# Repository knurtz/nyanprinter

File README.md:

# NyanPrinter
This printer runs on STM32F103 and it prints AND plays the nyan cat!

## Idea

Thermal printers make a lot of noise while printing -- everyone, who has bought something from a shop with one of those old cash registers knows that! At the heart of such a printer lies of course a stepper motor. Making music with stepper motors is an old thing in the Arduino community. But as far as I know, nobody has ever tried to make music AND print something at the same time -- until now!

Getting picture and sound to line up is not particulary easy, because there are certain limitations to the printing speed of a thermal printer -- and thus also for the maximum pitch we can get out of the machine. 

The datasheet recommends an approximate exposure of 1 ms per line, which responds to a 1 kHz pitch. This is, unless more than 64 pixels out of the total 384 pixels per line are printed simultanously. Here we need to do devided printing, which means multiple exposure bursts for one single line. This is where things get tricky. I need to let the printer run at a fixed speed and cannot stop at a line just because I want to print more than 64 pixels. Otherwise I would get a sudden break in my music.

This is the solution I came up with: If the printer encounters a line with more than 64 pixels, it prints the first 64 (or less) pixels, then advances the motor one step, going back one step immediately in order to print the next 64 pixels and so on. I have not yet tested, if the sudden change in direction is audible. If so, I might have to change it up a little bit and print multiple lines first, then go back over them a second time.

## Hardware

- STM32F103 Bluepill Development Board: [stm32duino.com](https://web.archive.org/web/20190524151648/https://wiki.stm32duino.com/index.php?title=Blue_Pill)
- Thermal printer MATSUSHITA EPL1801S2E from [pollin.de](https://www.pollin.de/p/thermo-druckelement-matsushita-epl1801s2e-721066)
- an awesome huge blue push button from [Amazon](https://www.amazon.de/gp/product/B07BSFMZJ2) (it lights up, too!)
- A4988 stepper motor driver board like this one from [pololu.com](https://www.pololu.com/product/1182)
- RECOM R-78E5.0-0.5 DC/DC converter from [conrad.de](https://www.conrad.de/de/recom-r-78e50-05-dcdc-wandler-print-24-vdc-5-vdc-500-ma-anzahl-ausgaenge-1-x-157954.html?)
- MAX6966 led driver from [farnell.com](https://de.farnell.com/maxim-integrated-products/max6966aee/led-treiber-mit-i-o-erweiterung/dp/2516036) for fancy led stuff
- custom milled PCB with some additional components like resistors and capacitors (Eagle files following shortly)
- custom enclosure printed with the amazing Vertigo Starlight filament from [filamentworld.de](https://www.filamentworld.de/shop/pla-filament-3d-drucker/pla-filament-1-75-mm-vertigo-starlight-075-kg/) (STL files following shortly as well)

## Software

I wanted to learn more about hardware peripherals of the STM32 family in this project. This is why I use a total of 3 timers, 2 DMA channels, one SPI and one UART peripheral. Things could have probably be done less complicated, but I would not have learned anything the easy way.

TIM2 is responsible for the motor step signal. It runs at a frequency that is determined by the current pitch of the music. The motor driver makes a step at every rising edge of the signal. Also, the printer needs to advance two steps for every line. Because of that, at every update interrupt of TIM2 (which corresponds to every step of the motor) I alternate between sending new data to the printer (triggering TIM1) and starting the exposure (triggering TIM3).

Data transfer is timed by TIM1, which triggers 64 DMA requests (64 transfers * 6 "pixels" per transfer = 384 pixels per line). The DMA sends the data to 6 parallel data lines that go into 6 shift registers inside the printer. Data alignment looks weird, this is why I wrote a small python script to convert images to a special byte array.

Finally TIM3 creates a pulse that corresponds to the needed exposure time of about 750 - 1000 us (depending on the supply voltage).

UART is needed for debugging and SPI for the led driver.

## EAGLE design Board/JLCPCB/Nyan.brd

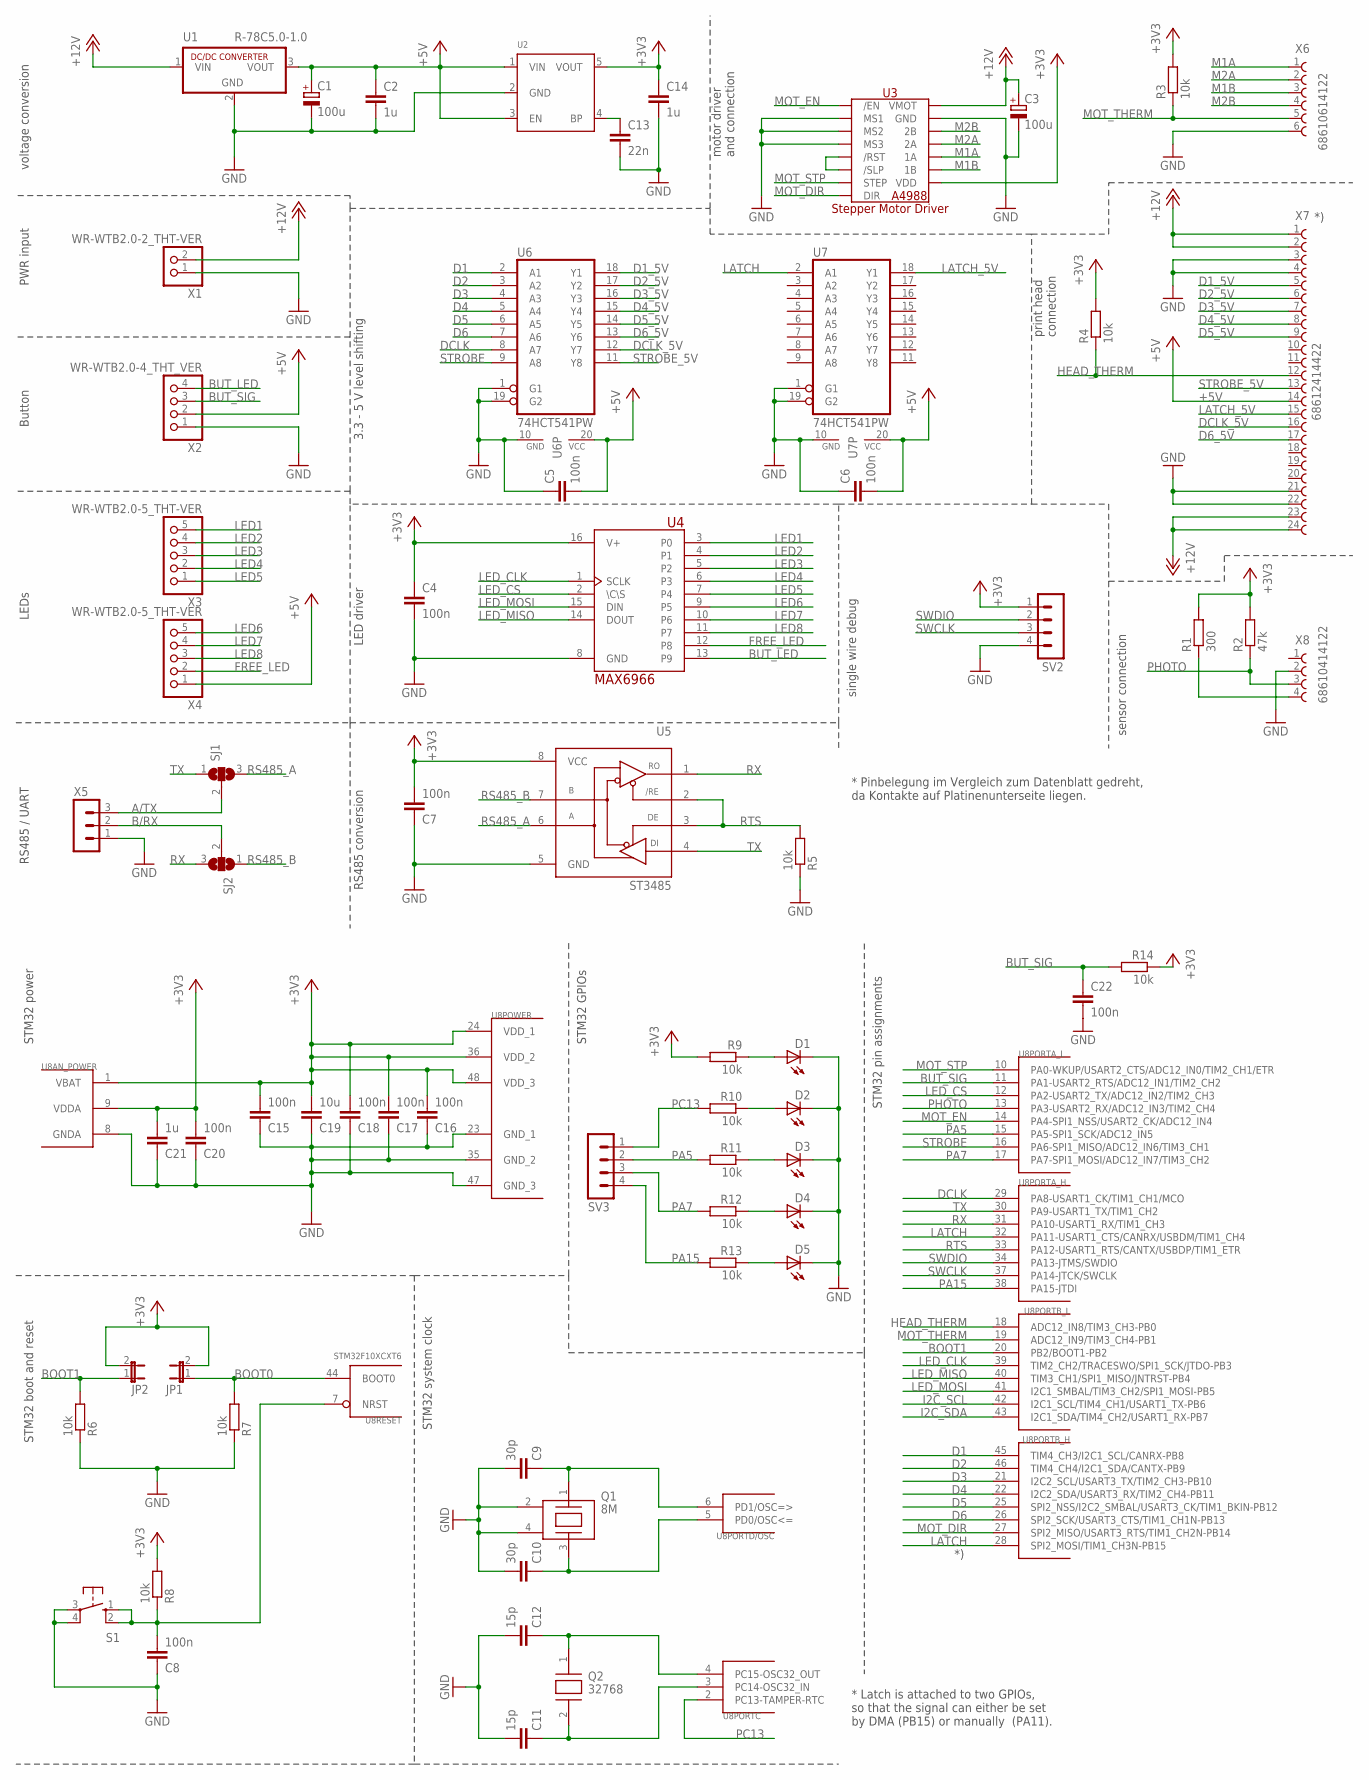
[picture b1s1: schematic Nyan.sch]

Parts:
C1, C3: 100u; E2,5-6
C2, C14, C21: 1u; C0603
C4, C5, C6, C7, C8, C15, C16, C17, C18, C20, C22: 100n; C0603
C9, C10: 30p; C0603
C11, C12: 15p; C0603
C13: 22n; C0603
C19: 10u; C0603
D1, D2, D3, D4, D5: LEDCHIP-LED0603; CHIP-LED0603
JP1, JP2: JP1E; JP1
Q1: 8M; SMD_5X3.2
Q2: 32768; SMD_3.2X1.5
R1: 300; R0603
R2: 47k; R0603
R3, R4, R5, R6, R7, R8, R9, R10, R11, R12, R13, R14: 10k; R0603
S1: 6X6_MOMENTARY_SWITCH
SJ1, SJ2: SJ2W; SJ_2
SV2, SV3: MA04-1ROUND_PAD; MA04-1_ROUND
U1: R-78C5.0-1.0; SIP3
U2: RT9193; SOT23-5
U3: A4988_STEP
U4: MAX6966; QSOP-16
U5: ST3485; SO-08
U6, U7: 74HCT541PW; TSSOP20
U8: STM32F10XCXT6; TQFP48
X1: WR-WTB2.0-2_THT-VER; WR-WTB2.0-2-THT-VER
X2: WR-WTB2.0-4_THT_VER; WR-WTB2.0-4-THT-VER
X3, X4: WR-WTB2.0-5_THT-VER; WR-WTB2.0-5-THT-VER
X5: MA03-1ROUND_PAD; MA03-1_ROUND
X6: 68610614122
X7: 68612414422
X8: 68610414122

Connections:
+3V3: C4.1, C7.2, C14.1, C15.2, C16.2, C17.2, C18.2, C19.2, C20.2, C21.2, JP1.2, JP2.2, R1.2, R2.2, R3.2, R4.2, R8.2, R9.2, R14.1, SV2.1, U2.5 (VOUT), U3.VDD, U4.16 (V+), U5.8 (VCC), U8.1 (VBAT), U8.9 (VDDA), U8.24 (VDD_1), U8.36 (VDD_2), U8.48 (VDD_3)
+5V: C1.+, C2.1, C5.2, C6.2, U1.3 (VOUT), U2.1 (VIN), U2.3 (EN), U6.20 (VCC), U7.20 (VCC), X2.2, X4.1, X7.14
+12V: C3.+, U1.1 (VIN), U3.VMOT, X1.2, X7.1, X7.2, X7.23, X7.24
A/TX: SJ1.2, X5.3
B/RX: SJ2.2, X5.2
BOOT0: JP1.1, R7.2, U8.44 (BOOT0)
BOOT1: JP2.1, R6.2, U8.20 (PB2/BOOT1-PB2)
BUT_LED: U4.13 (P9), X2.4
BUT_SIG: C22.1, R14.2, U8.11 (PA1-USART2_RTS/ADC12_IN1/TIM2_CH2), X2.3
D1: U6.2 (A1), U8.45 (TIM4_CH3/I2C1_SCL/CANRX-PB8)
D1_5V: U6.18 (Y1), X7.5
D2: U6.3 (A2), U8.46 (TIM4_CH4/I2C1_SDA/CANTX-PB9)
D2_5V: U6.17 (Y2), X7.6
D3: U6.4 (A3), U8.21 (I2C2_SCL/USART3_TX/TIM2_CH3-PB10)
D3_5V: U6.16 (Y3), X7.7
D4: U6.5 (A4), U8.22 (I2C2_SDA/USART3_RX/TIM2_CH4-PB11)
D4_5V: U6.15 (Y4), X7.8
D5: U6.6 (A5), U8.25 (SPI2_NSS/I2C2_SMBAL/USART3_CK/TIM1_BKIN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)
D5_5V: U6.14 (Y5), X7.9
D6: U6.7 (A6), U8.26 (SPI2_SCK/USART3_CTS/TIM1_CH1N-PB13)
D6_5V: U6.13 (Y6), X7.17
DCLK: U6.8 (A7), U8.29 (PA8-USART1_CK/TIM1_CH1/MCO)
DCLK_5V: U6.12 (Y7), X7.16
FREE_LED: U4.12 (P8), X4.2
GND: C1.-, C2.2, C3.-, C4.2, C5.1, C6.1, C7.1, C8.1, C9.2, C10.2, C11.2, C12.2, C13.2, C14.2, C15.1, C16.1, C17.1, C18.1, C19.1, C20.1, C21.1, C22.2, D1.C, D2.C, D3.C, D4.C, D5.C, Q1.2, Q1.4, R5.1, R6.1, R7.1, S1.3, S1.4, SV2.4, U1.2 (GND), U2.2 (GND), U3.GND, U3.GND2 (GND), U3.MS1, U3.MS2, U3.MS3, U4.8 (GND), U5.5 (GND), U6.1 (G1), U6.10 (GND), U6.19 (G2), U7.1 (G1), U7.10 (GND), U7.19 (G2), U8.8 (GNDA), U8.23 (GND_1), U8.35 (GND_2), U8.47 (GND_3), X1.1, X2.1, X5.1, X6.6, X7.3, X7.4, X7.21, X7.22, X8.2
HEAD_THERM: R4.1, U8.18 (ADC12_IN8/TIM3_CH3-PB0), X7.12
I2C_SCL: U8.42 (I2C1_SCL/TIM4_CH1/USART1_TX-PB6)
I2C_SDA: U8.43 (I2C1_SDA/TIM4_CH2/USART1_RX-PB7)
LATCH: U7.2 (A1), U8.28 (SPI2_MOSI/TIM1_CH3N-PB15), U8.32 (PA11-USART1_CTS/CANRX/USBDM/TIM1_CH4)
LATCH_5V: U7.18 (Y1), X7.15
LED1: U4.3 (P0), X3.5
LED2: U4.4 (P1), X3.4
LED3: U4.5 (P2), X3.3
LED4: U4.6 (P3), X3.2
LED5: U4.7 (P4), X3.1
LED6: U4.9 (P5), X4.5
LED7: U4.10 (P6), X4.4
LED8: U4.11 (P7), X4.3
LED_CLK: U4.1 (SCLK), U8.39 (TIM2_CH2/TRACESWO/SPI1_SCK/JTDO-PB3)
LED_CS: U4.2 (\C\S), U8.12 (PA2-USART2_TX/ADC12_IN2/TIM2_CH3)
LED_MISO: U4.14 (DOUT), U8.40 (TIM3_CH1/SPI1_MISO/JNTRST-PB4)
LED_MOSI: U4.15 (DIN), U8.41 (I2C1_SMBAL/TIM3_CH2/SPI1_MOSI-PB5)
M1A: U3.1A, X6.1
M1B: U3.1B, X6.3
M2A: U3.2A, X6.2
M2B: U3.2B, X6.4
MOT_DIR: U3.DIR, U8.27 (SPI2_MISO/USART3_RTS/TIM1_CH2N-PB14)
MOT_EN: U3./EN, U8.14 (PA4-SPI1_NSS/USART2_CK/ADC12_IN4)
MOT_STP: U3.STEP, U8.10 (PA0-WKUP/USART2_CTS/ADC12_IN0/TIM2_CH1/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)
MOT_THERM: R3.1, U8.19 (ADC12_IN9/TIM3_CH4-PB1), X6.5
unnamed: R1.1, X8.4
unnamed: U3./RST, U3./SLP
unnamed: C8.2, R8.1, S1.1, S1.2, U8.7 (NRST)
unnamed: C12.1, Q2.1, U8.4 (PC15-OSC32_OUT)
unnamed: C11.1, Q2.2, U8.3 (PC14-OSC32_IN)
unnamed: C10.1, Q1.3, U8.5 (PD0/OSC<=)
unnamed: C9.1, Q1.1, U8.6 (PD1/OSC=>)
unnamed: D4.A, R12.1
unnamed: D1.A, R9.1
unnamed: D2.A, R10.1
unnamed: D3.A, R11.1
unnamed: C13.1, U2.4 (BP)
unnamed: D5.A, R13.1
PA5: R11.2, SV3.2, U8.15 (PA5-SPI1_SCK/ADC12_IN5)
PA7: R12.2, SV3.3, U8.17 (PA7-SPI1_MOSI/ADC12_IN7/TIM3_CH2)
PA15: R13.2, SV3.4, U8.38 (PA15-JTDI)
PC13: R10.2, SV3.1, U8.2 (PC13-TAMPER-RTC)
PHOTO: R2.1, U8.13 (PA3-USART2_RX/ADC12_IN3/TIM2_CH4), X8.3
RS485_A: SJ1.3, U5.6 (A)
RS485_B: SJ2.1, U5.7 (B)
RTS: R5.2, U5.2 (!RE), U5.3 (DE), U8.33 (PA12-USART1_RTS/CANTX/USBDP/TIM1_ETR)
RX: SJ2.3, U5.1 (RO), U8.31 (PA10-USART1_RX/TIM1_CH3)
STROBE: U6.9 (A8), U8.16 (PA6-SPI1_MISO/ADC12_IN6/TIM3_CH1)
STROBE_5V: U6.11 (Y8), X7.13
SWCLK: SV2.3, U8.37 (PA14-JTCK/SWCLK)
SWDIO: SV2.2, U8.34 (PA13-JTMS/SWDIO)
TX: SJ1.1, U5.4 (DI), U8.30 (PA9-USART1_TX/TIM1_CH2)

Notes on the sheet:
Button
PWR input
LEDs
RS485 / UART
* Latch is attached to two GPIOs, so that the signal can either be set by DMA (PB15) or manually (PA11).
* Pinbelegung im Vergleich zum Datenblatt gedreht, da Kontakte auf Platinenunterseite liegen.
voltage conversion
LED driver
RS485 conversion
3.3 - 5 V level shifting
motor driver and connection
print head connection
sensor connection
single wire debug
STM32 power
STM32 boot and reset
STM32 system clock
STM32 GPIOs
STM32 pin assignments

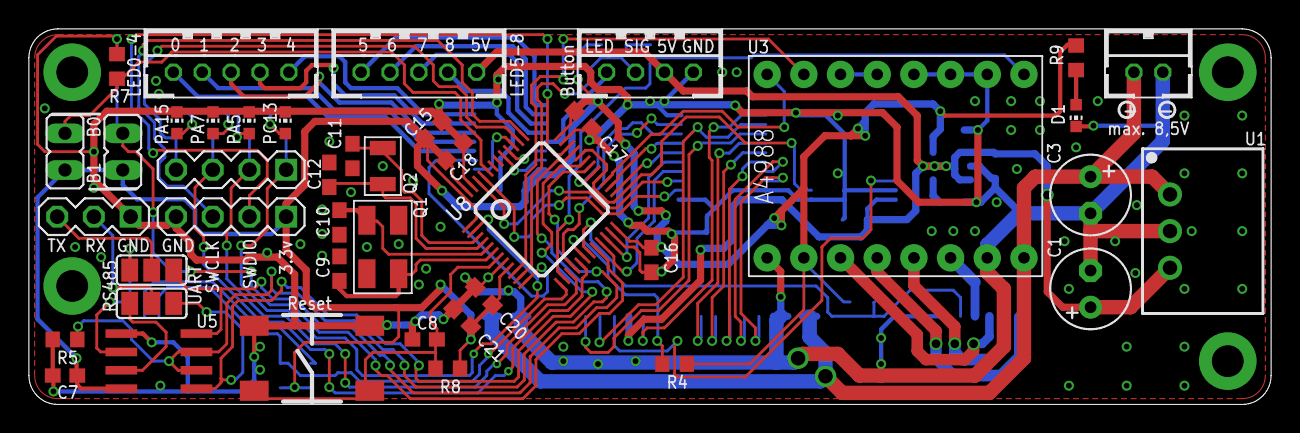
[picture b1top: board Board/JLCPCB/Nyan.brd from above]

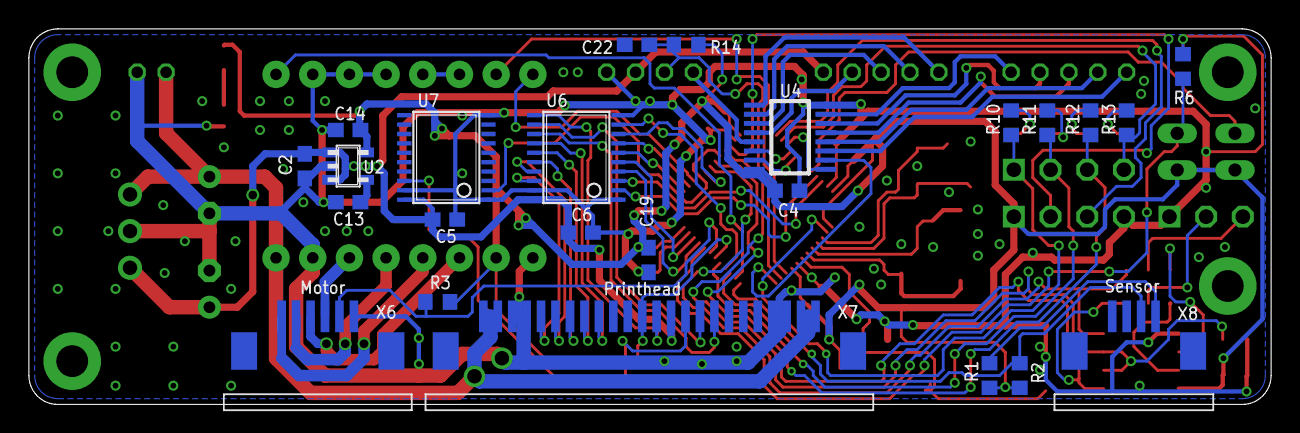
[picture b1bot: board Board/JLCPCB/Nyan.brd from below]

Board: 2 copper layers, 86.0 x 26.0 mm, 66 parts (24 on the bottom side), 75 nets.

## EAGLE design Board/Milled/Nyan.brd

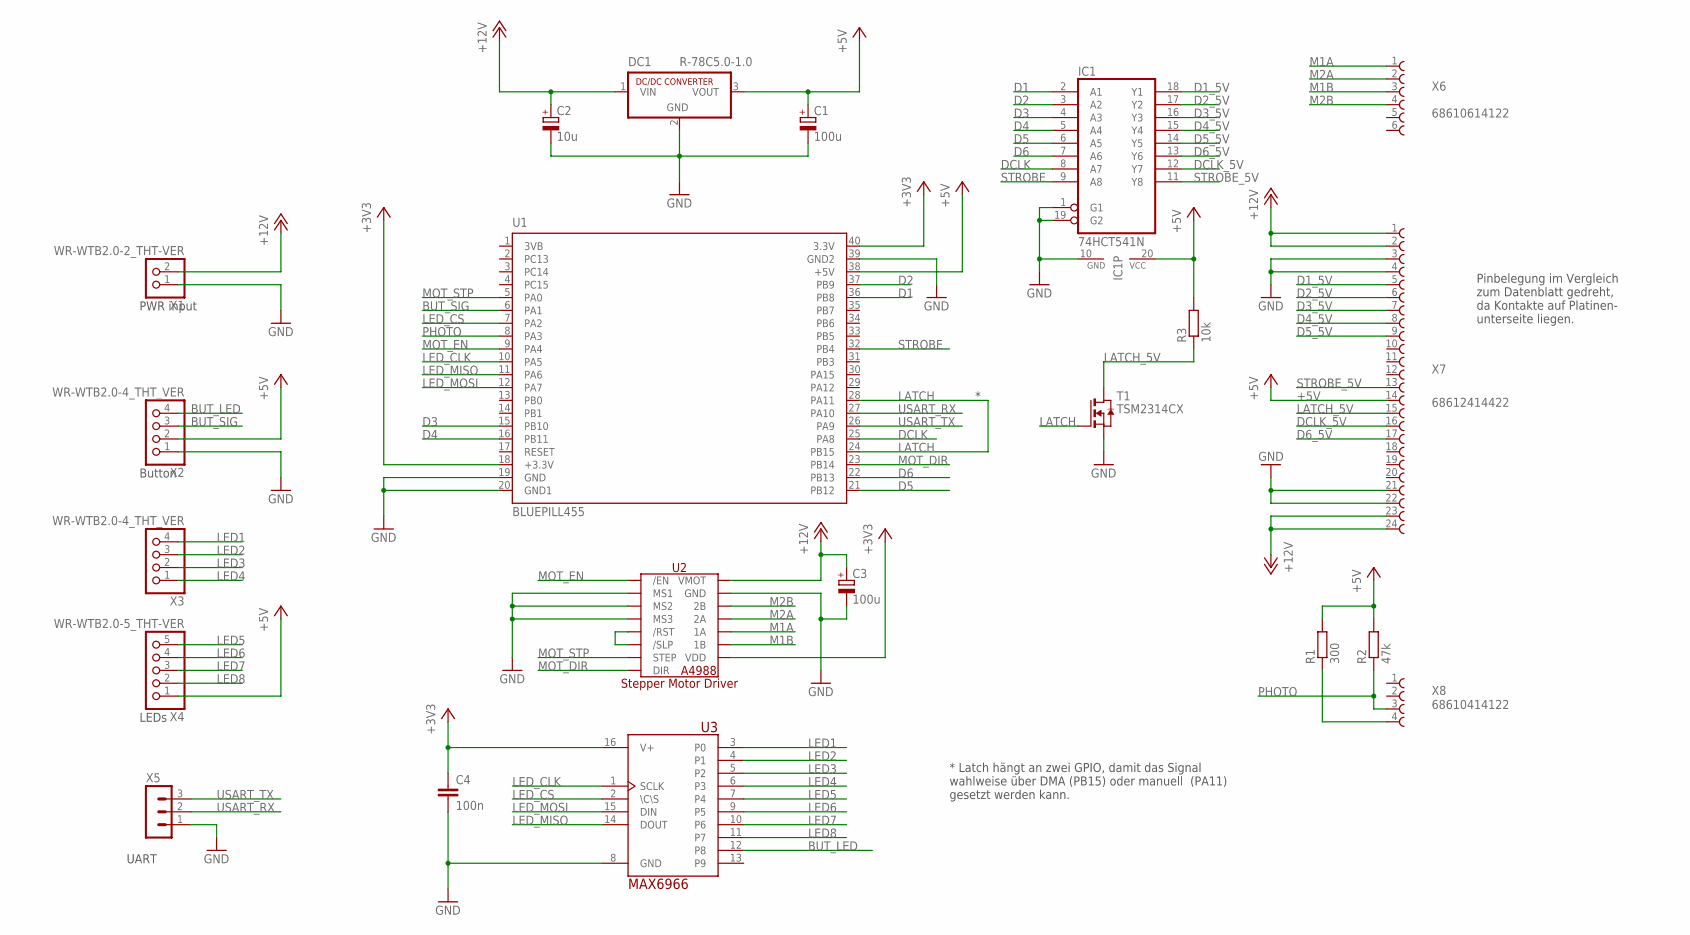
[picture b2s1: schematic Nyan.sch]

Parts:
C1, C3: 100u; E2,5-6
C2: 10u; E2,5-6
C4: 100n; C075-032X103
DC1: R-78C5.0-1.0; SIP3
IC1: 74HCT541N; DIL20
R1: 300; 0204/7
R2: 47k; 0204/7
R3: 10k; R0603
T1: TSM2314CX; SOT-23
U1: BLUEPILL455; DIL40
U2: A4988_STEP
U3: MAX6966; QSOP-16
X1: WR-WTB2.0-2_THT-VER; WR-WTB2.0-2-THT-VER
X2, X3: WR-WTB2.0-4_THT_VER; WR-WTB2.0-4-THT-VER
X4: WR-WTB2.0-5_THT-VER; WR-WTB2.0-5-THT-VER
X5: MA03-1ROUND_PAD; MA03-1_ROUND
X6: 68610614122
X7: 68612414422
X8: 68610414122

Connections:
+3V3: C4.1, U1.18 (+3.3V), U1.40 (3.3V), U2.VDD, U3.16 (V+)
+5V: C1.+, DC1.3 (VOUT), IC1.20 (VCC), R1.2, R2.2, R3.2, U1.38 (+5V), X2.2, X4.1, X7.14
+12V: C2.+, C3.+, DC1.1 (VIN), U2.VMOT, X1.2, X7.1, X7.2, X7.23, X7.24
BUT_LED: U3.12 (P8), X2.4
BUT_SIG: U1.6 (PA1), X2.3
D1: IC1.2 (A1), U1.36 (PB8)
D1_5V: IC1.18 (Y1), X7.5
D2: IC1.3 (A2), U1.37 (PB9)
D2_5V: IC1.17 (Y2), X7.6
D3: IC1.4 (A3), U1.15 (PB10)
D3_5V: IC1.16 (Y3), X7.7
D4: IC1.5 (A4), U1.16 (PB11)
D4_5V: IC1.15 (Y4), X7.8
D5: IC1.6 (A5), U1.21 (PB12)
D5_5V: IC1.14 (Y5), X7.9
D6: IC1.7 (A6), U1.22 (PB13)
D6_5V: IC1.13 (Y6), X7.17
DCLK: IC1.8 (A7), U1.25 (PA8)
DCLK_5V: IC1.12 (Y7), X7.16
GND: C1.-, C2.-, C3.-, C4.2, DC1.2 (GND), IC1.1 (G1), IC1.10 (GND), IC1.19 (G2), T1.2 (S), U1.19 (GND), U1.20 (GND1), U1.39 (GND2), U2.GND, U2.GND2 (GND), U2.MS1, U2.MS2, U2.MS3, U3.8 (GND), X1.1, X2.1, X5.1, X7.3, X7.4, X7.21, X7.22
LATCH: T1.1 (G), U1.24 (PB15), U1.28 (PA11)
LATCH_5V: R3.1, T1.3 (D), X7.15
LED1: U3.3 (P0), X3.4
LED2: U3.4 (P1), X3.3
LED3: U3.5 (P2), X3.2
LED4: U3.6 (P3), X3.1
LED5: U3.7 (P4), X4.5
LED6: U3.9 (P5), X4.4
LED7: U3.10 (P6), X4.3
LED8: U3.11 (P7), X4.2
LED_CLK: U1.10 (PA5), U3.1 (SCLK)
LED_CS: U1.7 (PA2), U3.2 (\C\S)
LED_MISO: U1.11 (PA6), U3.14 (DOUT)
LED_MOSI: U1.12 (PA7), U3.15 (DIN)
M1A: U2.1A, X6.1
M1B: U2.1B, X6.3
M2A: U2.2A, X6.2
M2B: U2.2B, X6.4
MOT_DIR: U1.23 (PB14), U2.DIR
MOT_EN: U1.9 (PA4), U2./EN
MOT_STP: U1.5 (PA0), U2.STEP
unnamed: R1.1, X8.4
unnamed: U2./RST, U2./SLP
PB3: U1.31 (PB3)
PHOTO: R2.1, U1.8 (PA3), X8.3
STROBE: IC1.9 (A8), U1.32 (PB4)
STROBE_5V: IC1.11 (Y8), X7.13
USART_RX: U1.27 (PA10), X5.2
USART_TX: U1.26 (PA9), X5.3

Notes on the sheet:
Button
PWR input
LEDs
UART
* Latch hängt an zwei GPIO, damit das Signal wahlweise über DMA (PB15) oder manuell (PA11) gesetzt werden kann.
Pinbelegung im Vergleich zum Datenblatt gedreht, da Kontakte auf Platinen- unterseite liegen.

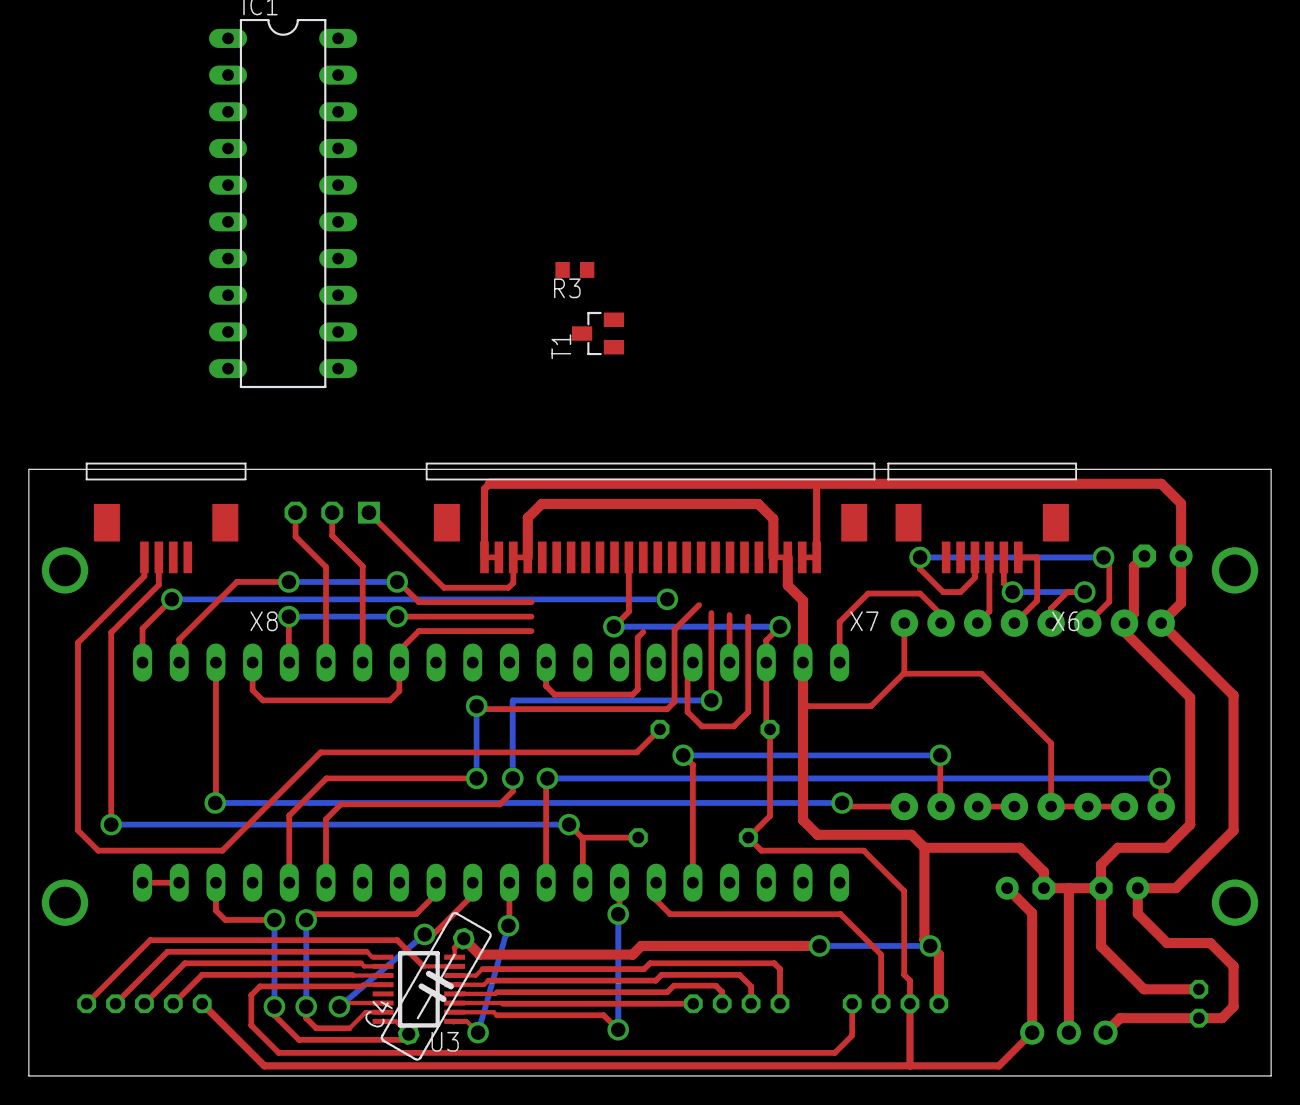
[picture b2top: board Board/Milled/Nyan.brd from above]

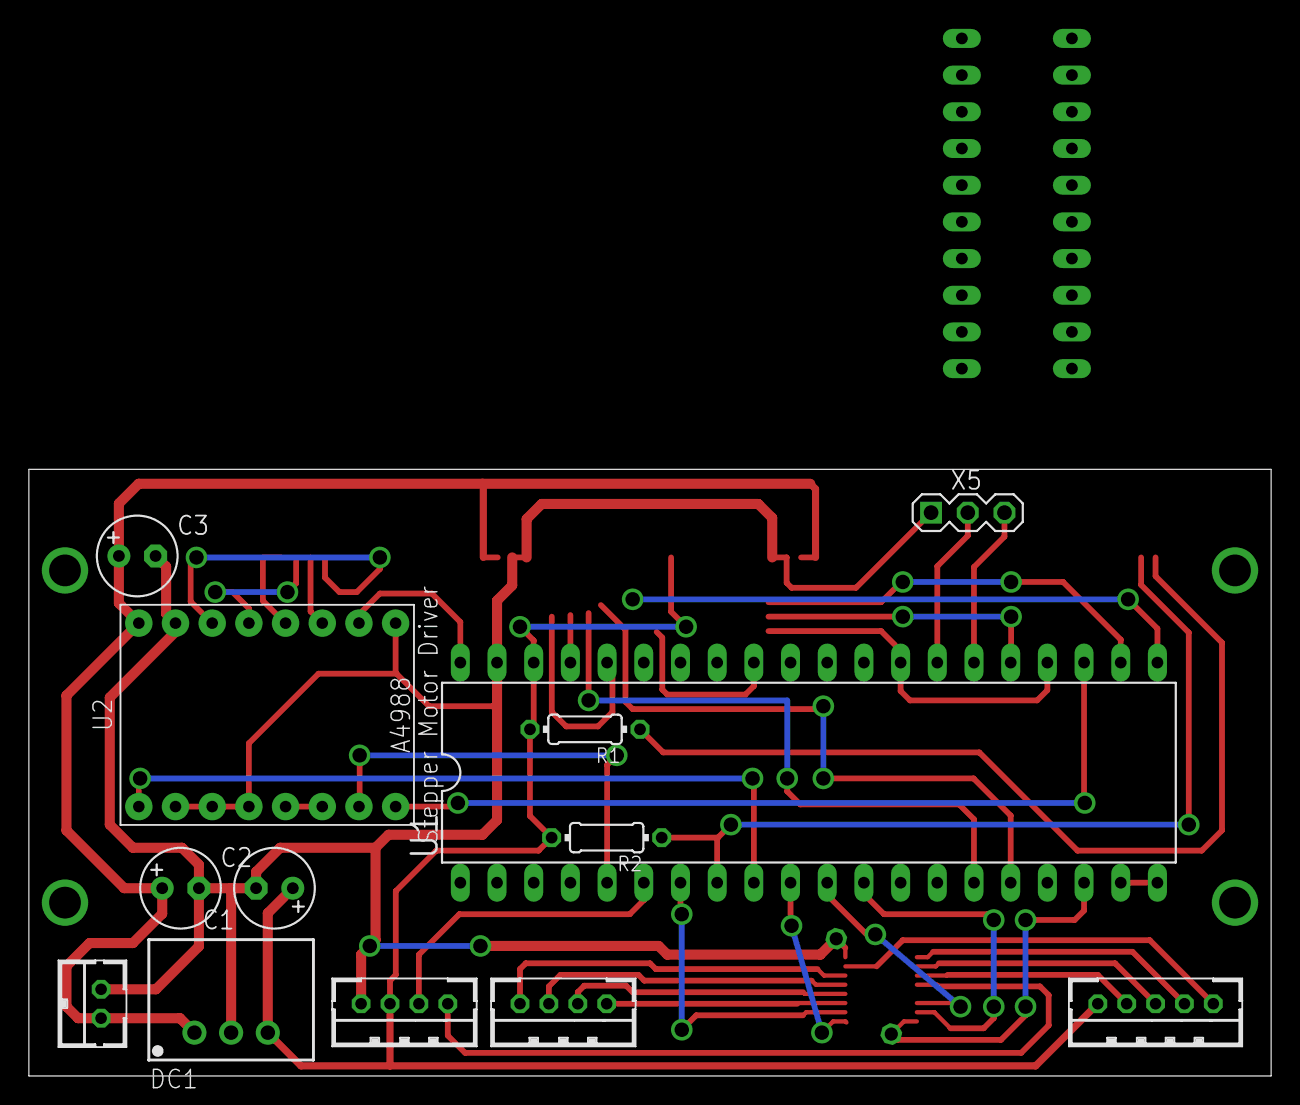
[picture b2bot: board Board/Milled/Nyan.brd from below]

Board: 2 copper layers, 86.0 x 42.0 mm, 21 parts (13 on the bottom side), 48 nets.

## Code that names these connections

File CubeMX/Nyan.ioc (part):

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Mcu.Name=STM32F103C(8-B)Tx
Mcu.Package=LQFP48
Mcu.UserName=STM32F103C8Tx
PA0-WKUP.GPIOParameters=GPIO_Label
PA0-WKUP.GPIO_Label=MOT_STP
PA0-WKUP.Signal=S_TIM2_CH1_ETR
PA1.GPIOParameters=GPIO_Label
PA1.GPIO_Label=BIG_BUTTON
PA1.Signal=GPIO_Input
PA10.Mode=Asynchronous
PA10.Signal=USART1_RX
PA11.GPIOParameters=GPIO_Label
PA11.GPIO_Label=LATCH
PA11.Signal=GPIO_Output
PA13.Mode=Serial_Wire
PA13.Signal=SYS_JTMS-SWDIO
PA14.Mode=Serial_Wire
PA14.Signal=SYS_JTCK-SWCLK
PA15.GPIOParameters=GPIO_Label
PA15.GPIO_Label=LED4
PA15.Signal=GPIO_Output
PA2.GPIOParameters=GPIO_Label
PA2.GPIO_Label=LED_CS
PA2.Signal=GPIO_Output
PA3.GPIOParameters=GPIO_Label
PA3.GPIO_Label=PHOTO
PA3.Signal=GPIO_Input
PA4.GPIOParameters=GPIO_Label
PA4.GPIO_Label=MOT_EN
PA4.Signal=GPIO_Output
PA5.GPIOParameters=GPIO_Label
PA5.GPIO_Label=LED2
PA5.Signal=GPIO_Output
PA6.GPIOParameters=GPIO_Label
PA6.GPIO_Label=STROBE
PA6.Signal=GPIO_Output
PA7.GPIOParameters=GPIO_Label
PA7.GPIO_Label=LED3
PA7.Signal=GPIO_Output
PA8.GPIOParameters=GPIO_Label
PA8.GPIO_Label=DCLK
PA8.Signal=GPIO_Output
PA9.Mode=Asynchronous
PA9.Signal=USART1_TX
PB0.GPIOParameters=GPIO_Label
PB0.GPIO_Label=HEAD_NTC
PB0.Signal=ADCx_IN8
PB1.GPIOParameters=GPIO_Label
PB1.GPIO_Label=MOT_NTC
PB1.Signal=ADCx_IN9
PB10.GPIOParameters=GPIO_Label
PB10.GPIO_Label=D3
PB10.Signal=GPIO_Output
PB11.GPIOParameters=GPIO_Label
PB11.GPIO_Label=D4
PB11.Signal=GPIO_Output
PB12.GPIOParameters=GPIO_Label
PB12.GPIO_Label=D5
PB12.Signal=GPIO_Output
PB13.GPIOParameters=GPIO_Label
PB13.GPIO_Label=D6
PB13.Signal=GPIO_Output
PB14.GPIOParameters=GPIO_Label
PB14.GPIO_Label=MOT_DIR
PB14.Signal=GPIO_Output
PB3.GPIOParameters=GPIO_Label
PB3.GPIO_Label=LED_CLK
PB3.Mode=Full_Duplex_Master
PB3.Signal=SPI1_SCK
PB4.GPIOParameters=GPIO_Label
PB4.GPIO_Label=LED_MISO
PB4.Mode=Full_Duplex_Master
PB4.Signal=SPI1_MISO
PB5.GPIOParameters=GPIO_Label
PB5.GPIO_Label=LED_MOSI
PB5.Mode=Full_Duplex_Master
PB5.Signal=SPI1_MOSI
PB8.GPIOParameters=GPIO_Label
PB8.GPIO_Label=D1
PB8.Signal=GPIO_Output
PB9.GPIOParameters=GPIO_Label
PB9.GPIO_Label=D2
PB9.Signal=GPIO_Output
PC13-TAMPER-RTC.GPIOParameters=GPIO_Label
PC13-TAMPER-RTC.GPIO_Label=LED1
PC13-TAMPER-RTC.Signal=GPIO_Output
RCC.SYSCLKFreq_VALUE=64000000
RCC.SYSCLKSource=RCC_SYSCLKSOURCE_PLLCLK
board=custom

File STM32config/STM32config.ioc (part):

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Mcu.Name=STM32F103C(8-B)Tx
Mcu.Package=LQFP48
Mcu.UserName=STM32F103C8Tx
PA0-WKUP.Signal=S_TIM2_CH1_ETR
PA1.Signal=GPXTI1
PA10.Mode=Asynchronous
PA10.Signal=USART1_RX
PA11.Signal=GPIO_Output
PA12.Mode=RTS_Only
PA12.Signal=USART1_RTS
PA13.Mode=Serial_Wire
PA13.Signal=SYS_JTMS-SWDIO
PA14.Mode=Serial_Wire
PA14.Signal=SYS_JTCK-SWCLK
PA15.Signal=GPIO_Output
PA2.Signal=GPIO_Output
PA3.Signal=GPIO_Input
PA4.Signal=GPIO_Output
PA5.Signal=GPIO_Output
PA6.Signal=S_TIM3_CH1
PA7.Signal=GPIO_Output
PA8.Signal=S_TIM1_CH1
PA9.Mode=Asynchronous
PA9.Signal=USART1_TX
PB0.Signal=ADCx_IN8
PB1.Signal=ADCx_IN9
PB10.Signal=GPIO_Output
PB11.Signal=GPIO_Output
PB12.Signal=GPIO_Output
PB13.Signal=GPIO_Output
PB14.Signal=GPIO_Output
PB15.Signal=GPIO_Output
PB3.Mode=Full_Duplex_Master
PB3.Signal=SPI1_SCK
PB4.Mode=Full_Duplex_Master
PB4.Signal=SPI1_MISO
PB5.Mode=Full_Duplex_Master
PB5.Signal=SPI1_MOSI
PB6.Mode=I2C
PB6.Signal=I2C1_SCL
PB7.Mode=I2C
PB7.Signal=I2C1_SDA
PB8.Signal=GPIO_Output
PB9.Signal=GPIO_Output
PC13-TAMPER-RTC.Signal=GPIO_Output
PC14-OSC32_IN.Mode=LSE-External-Oscillator
PC14-OSC32_IN.Signal=RCC_OSC32_IN
PC15-OSC32_OUT.Mode=LSE-External-Oscillator
PC15-OSC32_OUT.Signal=RCC_OSC32_OUT
PD0-OSC_IN.Mode=HSE-External-Oscillator
PD0-OSC_IN.Signal=RCC_OSC_IN
PD1-OSC_OUT.Mode=HSE-External-Oscillator
PD1-OSC_OUT.Signal=RCC_OSC_OUT
board=custom

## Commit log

2019-03-30 Code for initialising the timers done, basic picture format as 2d array set up
2019-04-01 Timer und DMA konfiguriert
2019-04-01 Datenblatt und Planungsdateien
2019-04-01 changed readme
2019-04-01 minor changed that didn't help te problem
2019-04-04 Motor dreht jetzt mit Timer PWM über CC1
2019-04-05 DMA transfer to GPIO works
2019-04-05 Python image analyzer copied from old Arduino project and modified for STM32 implementation
2019-04-05 Added some project information in readme.md
2019-04-05 Added printer name in readme
2019-04-05 Added image to code, test routine should work, doesn't :(
2019-04-05 Fixed something, but still not working. Probably because of voltage differences between STM and printer :(
2019-04-06 Eagle files for milled circuit board
2019-04-08 Current development state with hardware fixes for 3 to 5 volt level shifting
2019-04-11 Fixed PB4 being always high by disabling JTAG
2019-04-11 Everything in interrupt routine, no manual triggering anymore
2019-04-14 [Board] Copied board for manufacturing at JLCPCB. Big changes
2019-04-14 [Doku] Updated roadmap for new board (also english now)
2019-04-14 Added bluepill schematic as reference and STM32CubeMX Config files
2019-04-14 [Board] A little more layouting done
2019-04-22 [Board] Positioning done
2019-04-27 [Board] Fixed positions for half the components
2019-04-27 [Board] Fixed positioning done
2019-04-27 [Board] Some progress in routing
2019-04-27 [Board] Some more traces :)
2019-04-27 [Board] And even more traces
2019-04-28 [Board] More layouting done
2019-04-30 [Board] Layouting of first half (microcontroller side) done.
2019-05-01 [Board] More layouting
2019-05-03 [Board] almost complete, last gnd and 3v traces missing
2019-05-03 [Board] Layout done
2019-05-04 [Board] Silk Screen Top done
2019-05-04 [Board] Silk Screen Bottom done
2019-05-05 [Board] Silkscreen done, DRC checked
2019-05-05 [Board] Fixed connection for crystals
2019-05-06 [Board] Added debouncing circuitry for pushbutton
2019-05-06 [Board] Finished for manufacturing
2019-05-26 Project settings updated for Eclipse version 2019-03
2019-05-27 Moved a lot of functions to separate source files
2019-05-27 Minor tidy up
2019-05-28 Fixed misfiring interrupt. Test image works.
2019-05-28 [Converter] Added detection for too many black pixels
2019-06-04 Added function for pitch adjustment
2019-06-10 Corrected intentation for all files
2019-06-10 Added defines for note frequencies
2019-06-10 Counting down notes instead of up
2019-06-10 Test: Image data direction
2019-08-19 [Code] Separated image data into header and source files
2019-08-19 [Image Converter] Modified converter to support more than 64 pixels per line
2019-08-19 [Code] Small changes to support more than 64 pixels per line
2019-08-20 [Images] Added converted nyan images
2019-08-20 [Tone generation] Added preload feature for step timer, possibly fixing interrupted notes
2019-08-22 [Datasheets] Moved to separate folder, added MAX6966
2019-08-22 [Roadmap] Finally translated the rest of the file
2019-08-22 [SPI LED] Added defines and GPIO setup for SPI LED driver
2019-08-22 [STM32 Cube Config] Migrated to newer program version
2019-08-22 [SPI LED] Implemented initialization for SPI LED driver
2019-08-22 [Code] Added systick counter and interrupt to delay feature
2019-08-22 [Readme] Changed link to stm32duino.com to archive
2019-08-22 [Code] Added generator for breathing pattern
2019-08-22 [Code] Changed default motor direction
2019-08-22 [Code] Modified breathing pattern to accomodate minimum and maximum values of MAX6966 LED driver
2019-08-22 [Code] Removed left over declaration
2019-08-27 [Code] Fixed misspelled variable name
2019-08-27 [SPI LED] Breathing LED in main loop works
2019-08-27 [SPI LED] Changed breathing period to 4 seconds
2019-08-27 [SPI LED] 20 mA current for LEDs
2019-08-27 [Code] Added some rough features for music generation
2019-08-27 [Code] Changed image to nyan start
2019-08-31 [Code] Frame counter also counts down to avoid confusion
2019-08-31 [Code] Latch fixed active
2019-08-31 [Code] Back to working test image.
2019-09-02 [Test Immage] New test image, diagonal line
2019-09-02 [Code] Static offset to iamge buffer fixes misaligned line
2019-09-02 [Code] Back to nyan cat, 1/10th speed, finally a correct cat
2019-10-07 [Elipse Config] Language settings
2019-10-07 [Image Converter] Changed conerter so one line will always end after the first 64 colored pixels
2021-12-05 Added KiCAD for Bom
2021-12-05 Added CubeMX code
2021-12-19 Added timer for strobe
2021-12-19 Added photoshop file for printed image

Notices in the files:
parts and their libraries:
Wuerth_Elektronik_eiCan_03_ZIF_Connector: Copyright: Würth Elektronik
